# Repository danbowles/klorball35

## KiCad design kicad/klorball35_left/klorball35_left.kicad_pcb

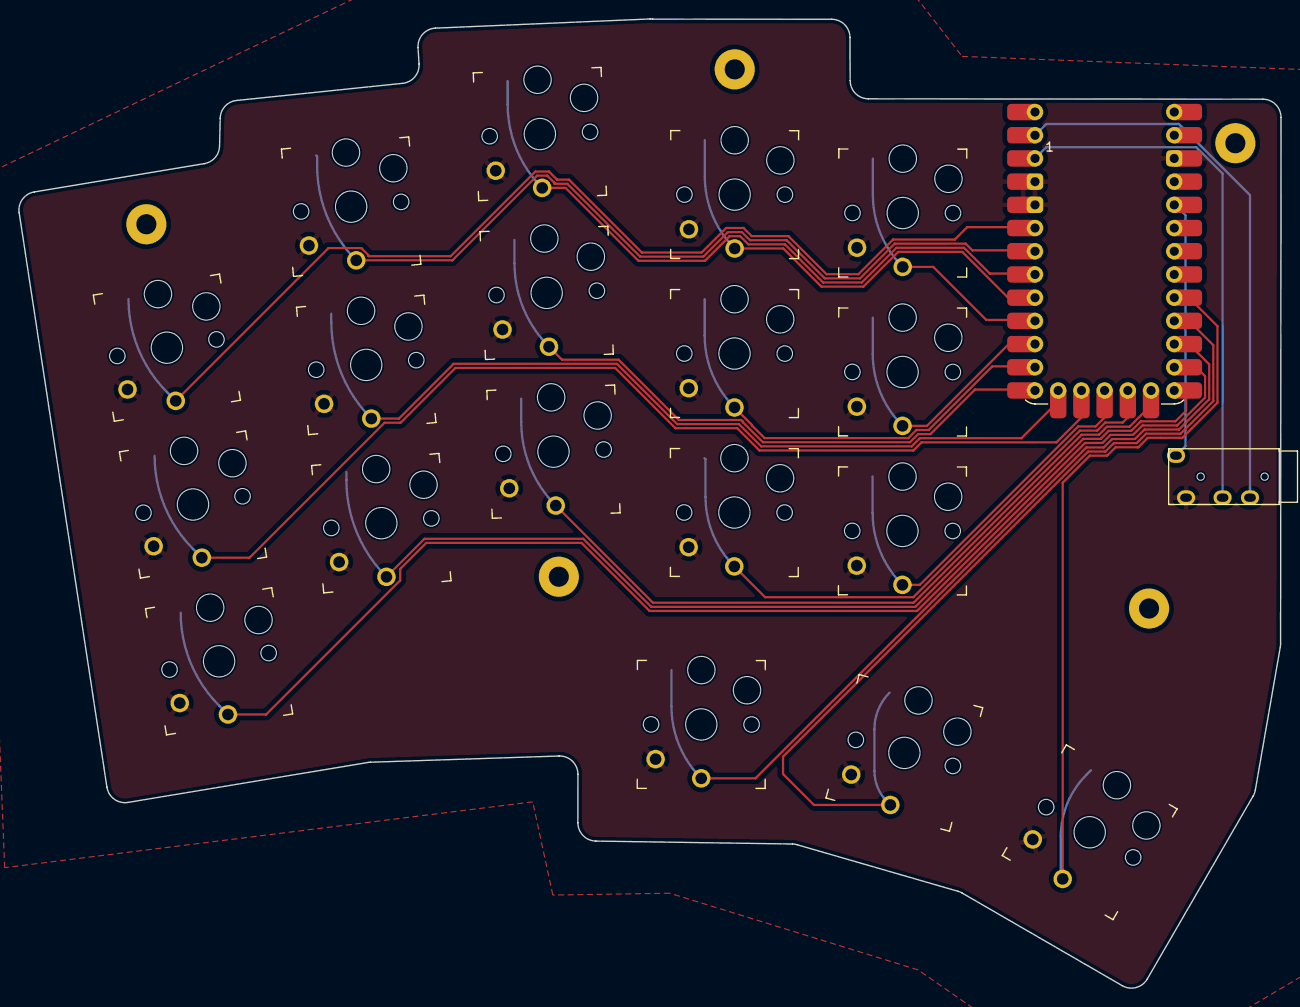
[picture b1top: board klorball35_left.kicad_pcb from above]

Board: 2 copper layers, 138.1 x 106.1 mm, 25 parts (0 on the bottom side), 22 nets.

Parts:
H1, H2, H3, H4, H5: MountingHole; MountingHole_2.2mm_M2_Pad
J1: TRRS; TRRS-PJ-320A
SW1, SW2, SW3, SW4, SW5, SW6, SW7, SW8, SW9, SW10, SW11, SW12, SW13, SW14, SW15, SW16, SW17, SW18: SW_Push; Kailh_socket_PG1350_optional
U1: Helios; Helios_ACH

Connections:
+3V3: J1.S, U1.16 (3V3)
/INDEX_BOTTOM: SW13.1, U1.28 (P15)
/INDEX_HOME: SW12.1, U1.11 (P8)
/INDEX_THUMB: SW14.1, U1.21 (P22)
/INDEX_TOP: SW11.1, U1.8 (P5)
/INNER_BOTTOM: SW17.1, U1.27 (P14)
/INNER_HOME: SW16.1, U1.10 (P7)
/INNER_THUMB: SW18.1, U1.20 (P26)
/INNER_TOP: SW15.1, U1.9 (P6)
/MIDDLE_BOTTOM: SW9.1, U1.29 (P16)
/MIDDLE_HOME: SW8.1, U1.12 (P9)
/MIDDLE_THUMB: SW10.1, U1.22 (P20)
/MIDDLE_TOP: SW7.1, U1.7 (P4)
/PINKY_BOTTOM: SW3.1, U1.23
/PINKY_HOME: SW2.1, U1.26 (P13)
/PINKY_TOP: SW1.1, U1.5 (P2)
/RING_BOTTOM: SW6.1, U1.24 (P21)
/RING_HOME: SW5.1, U1.25 (P12)
/RING_TOP: SW4.1, U1.6 (P3)
/TRRS_RX: J1.R1, U1.2 (P1)
/TRRS_TX: J1.R2, U1.1 (P0)
GND: J1.T, SW1.2, SW2.2, SW3.2, SW4.2, SW5.2, SW6.2, SW7.2, SW8.2, SW9.2, SW10.2, SW11.2, SW12.2, SW13.2, SW14.2, SW15.2, SW16.2, SW17.2, SW18.2, U1.3 (GND), U1.4 (GND), U1.14 (GND)

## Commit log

2025-12-15 🎉 Initial commit.
2025-12-29 ✨ Attempting the board design
2026-01-04 ✨ Board outline
2026-01-04 ✨ Trackball on the right!
2026-01-05 ✨ Left+right combo
2026-01-11 🔧 Mounting holes done for now.
2026-01-12 🎨 Fixing up holes for trackball mount
2026-01-12 📱 PCB'ing
2026-01-18 Attribute fixing
2026-01-18 Initial commit of PCB+pinky switches placed
2026-02-07 Finishing footprints on left, starting schema
2026-04-24 Finishing left, start of right
2026-05-12 finishing right, start of gerbers
2026-05-26 Wrapping up, re-organizing. Final gerbers and designs
2026-06-25 📝 Updating readme and images
